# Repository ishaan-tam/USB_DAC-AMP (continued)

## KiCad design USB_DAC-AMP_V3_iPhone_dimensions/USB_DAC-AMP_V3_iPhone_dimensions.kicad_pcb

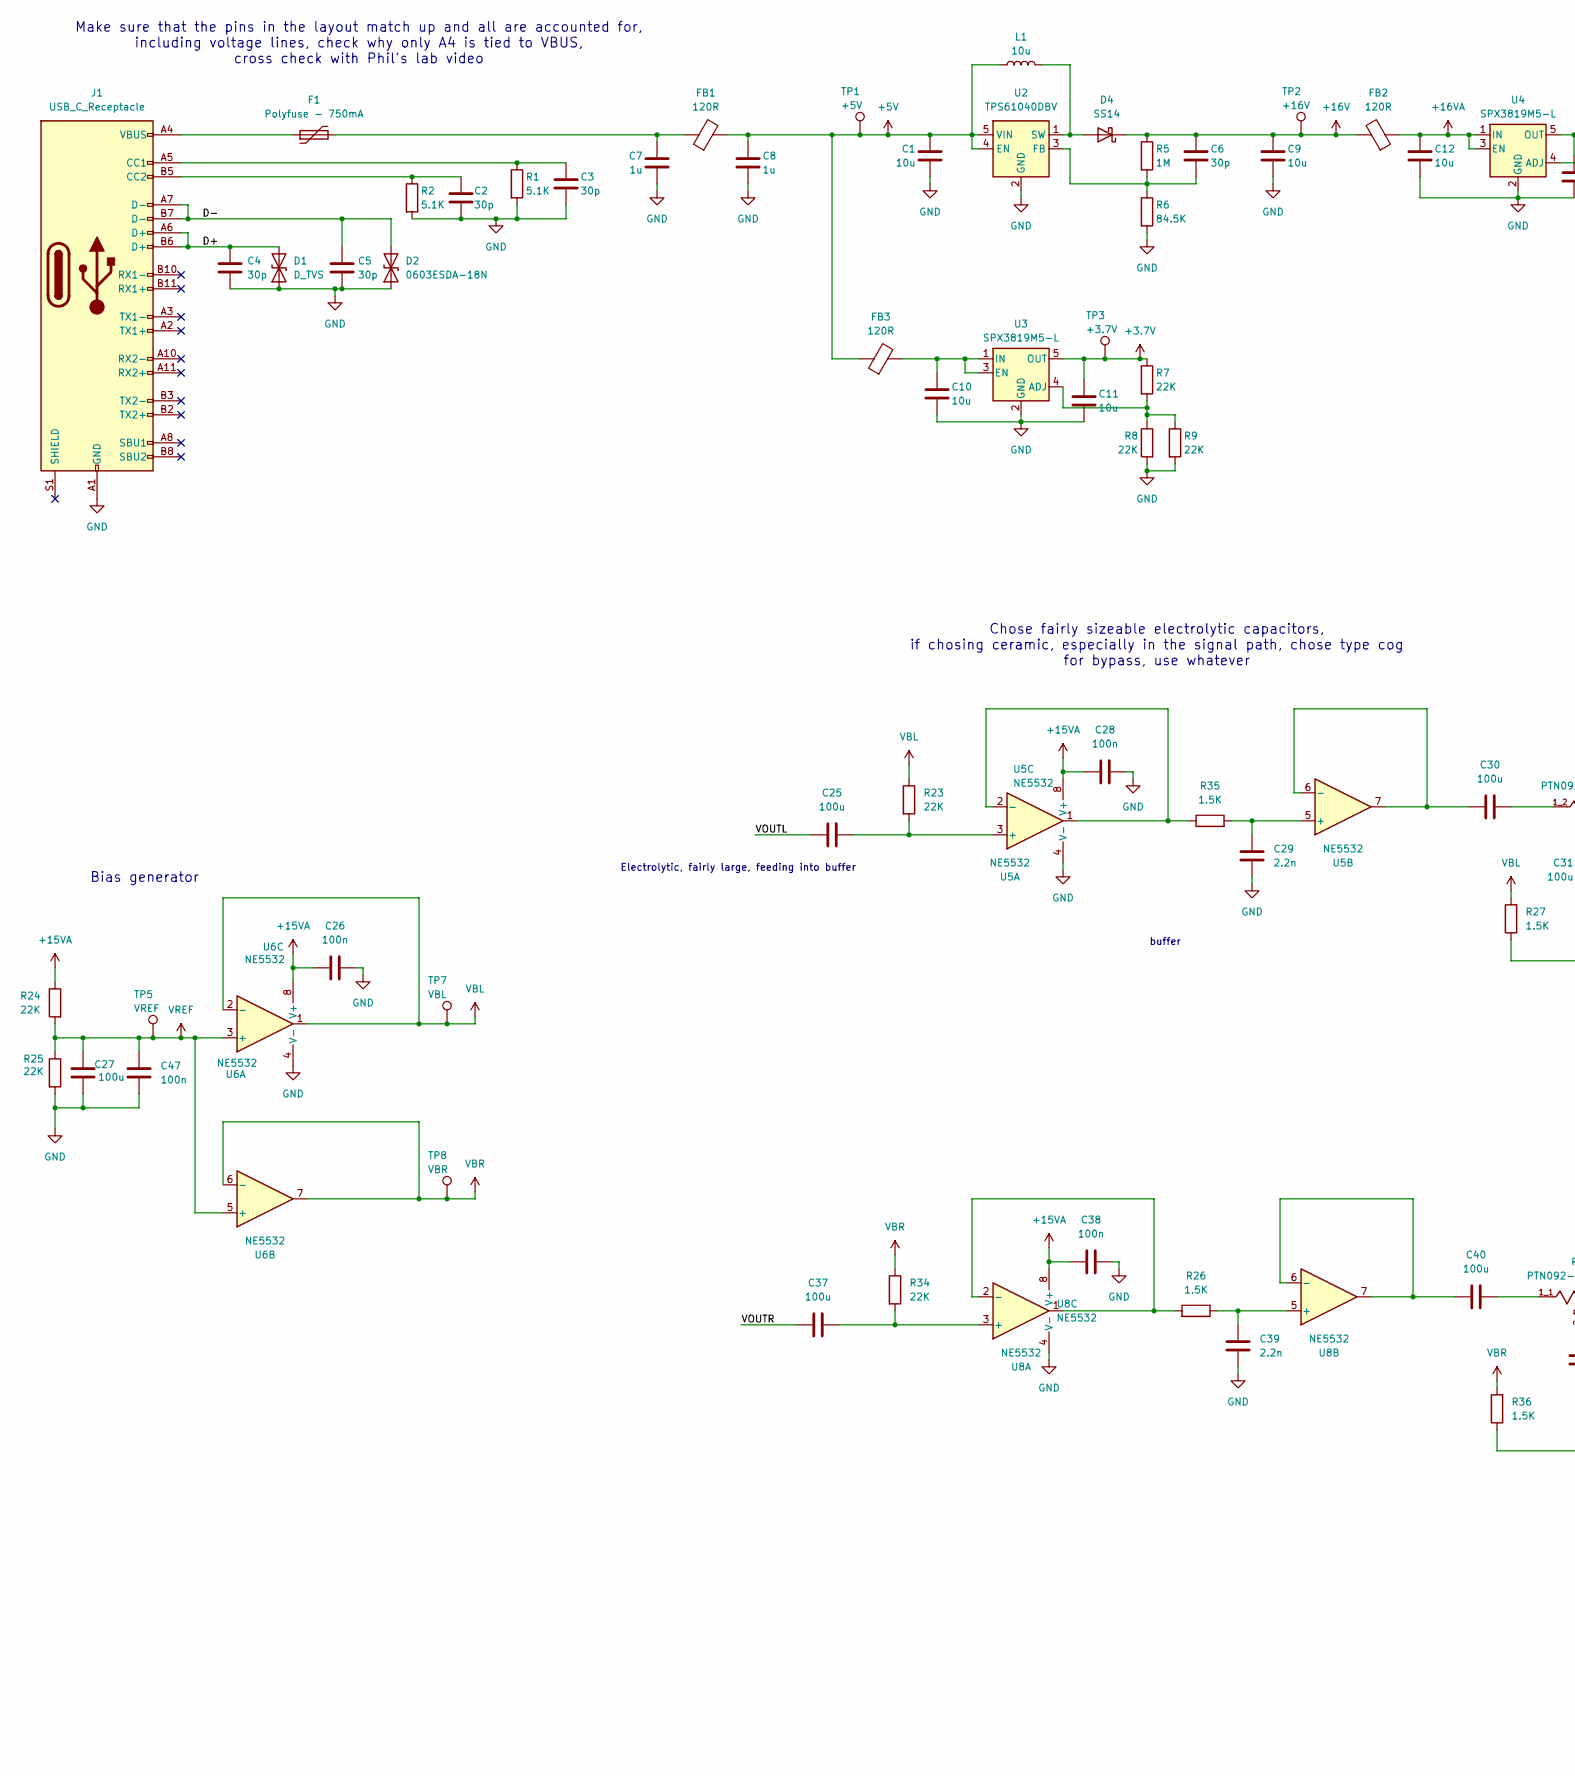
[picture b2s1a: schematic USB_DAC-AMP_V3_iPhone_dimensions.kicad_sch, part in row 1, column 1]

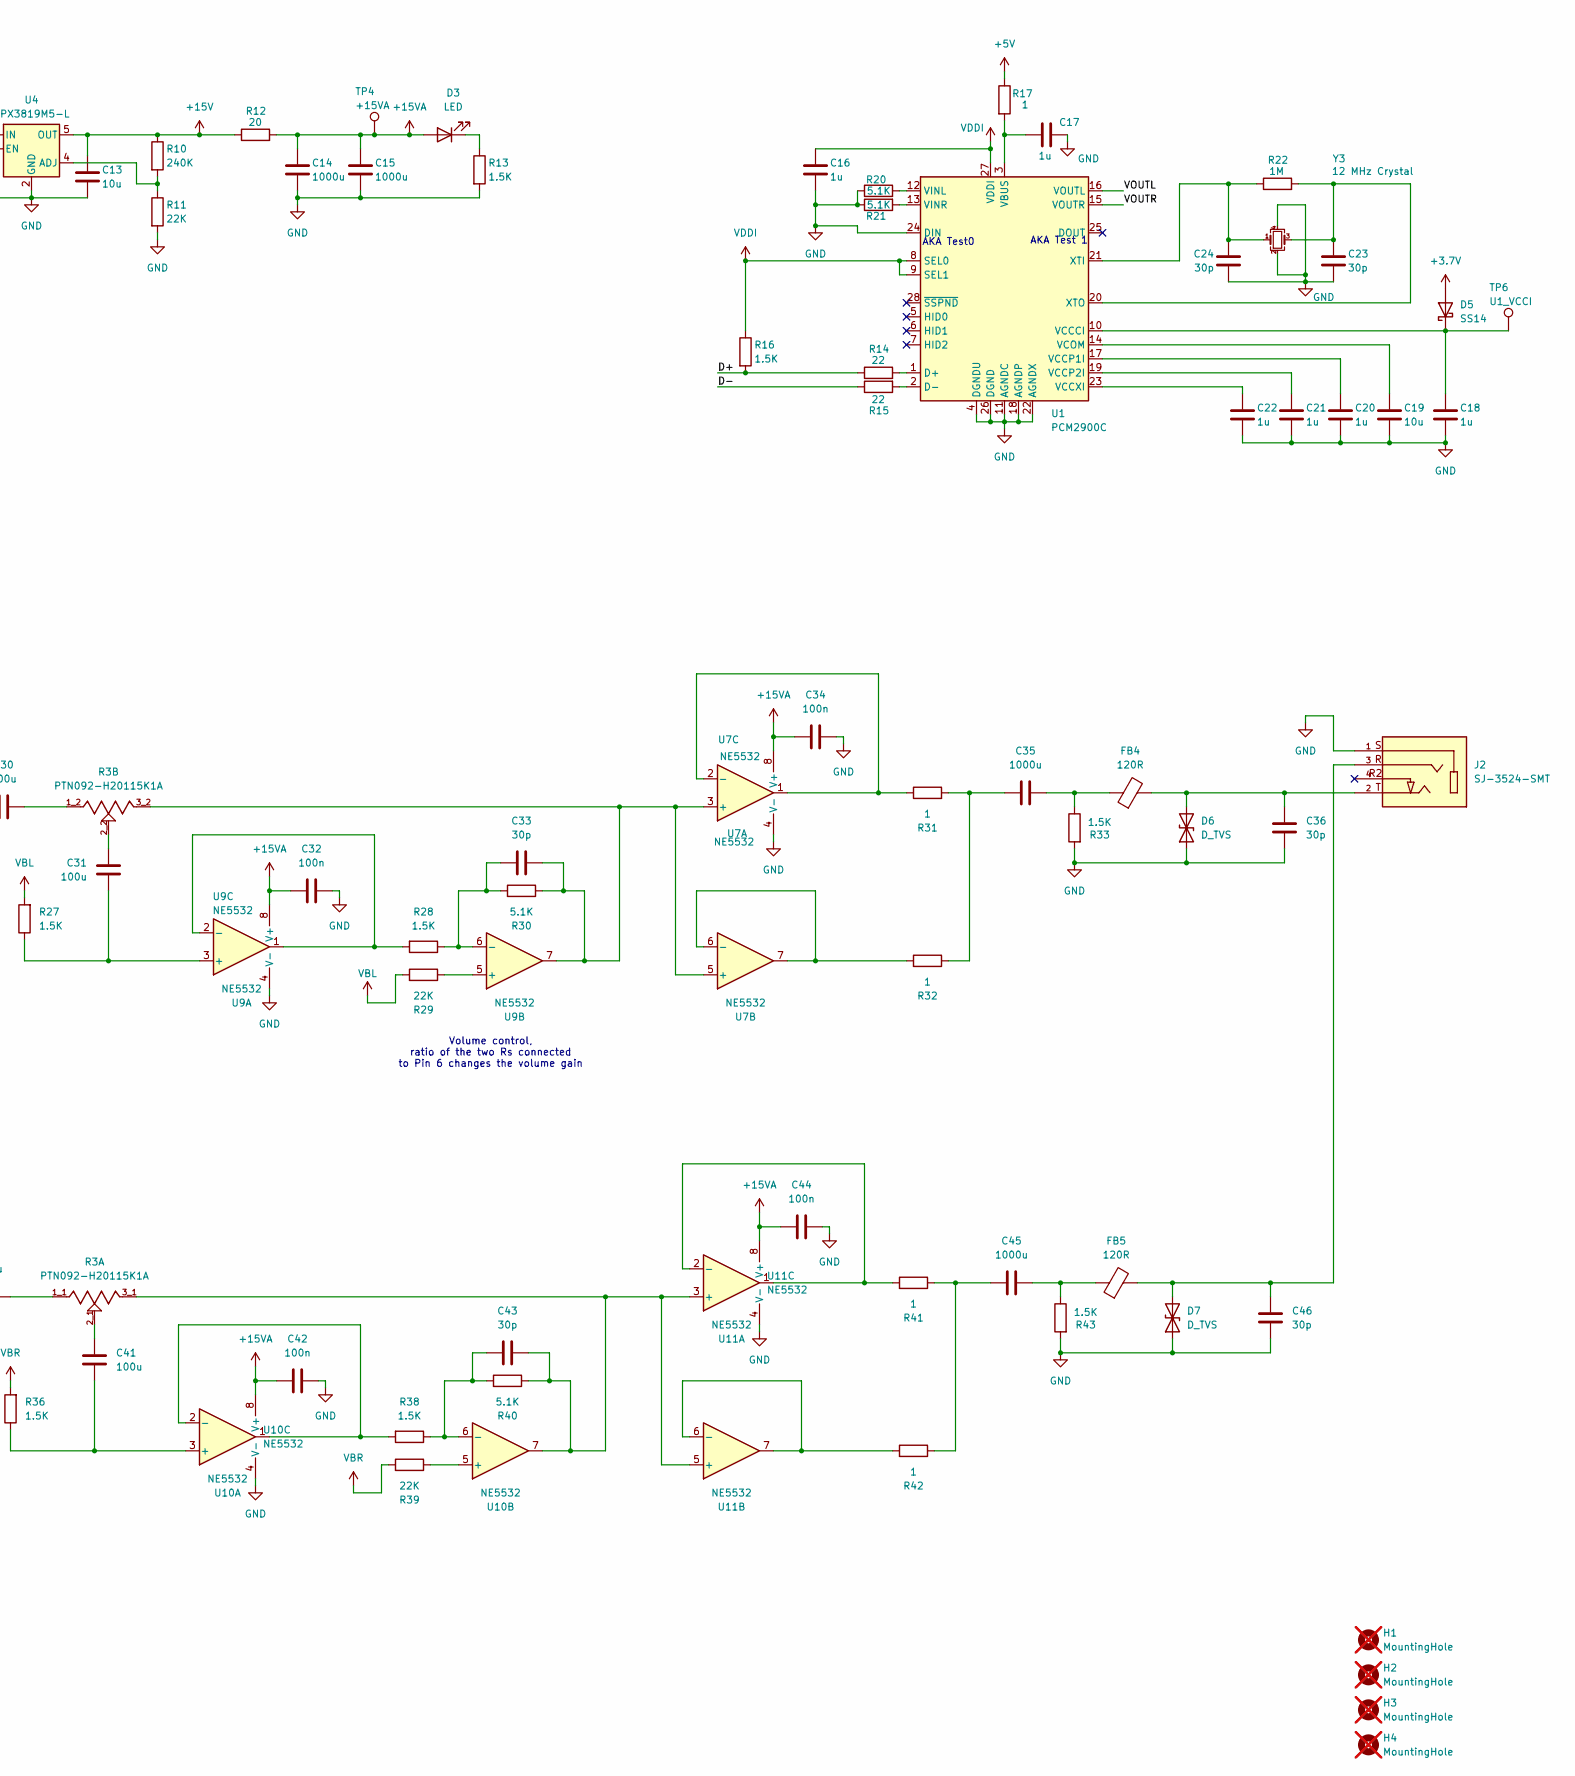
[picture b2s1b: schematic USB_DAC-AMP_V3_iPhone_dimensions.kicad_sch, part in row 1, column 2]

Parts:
C1, C9, C10, C11, C12, C13, C19: 10u; C_0603_1608Metric_Pad1.08x0.95mm_HandSolder; LCSC C1035
C2, C3, C4, C5, C6, C23, C24, C33, C36, C43, C46: 30p; C_0603_1608Metric_Pad1.08x0.95mm_HandSolder; LCSC C1658
C7, C8, C16, C17, C18, C20, C21, C22: 1u; C_0603_1608Metric_Pad1.08x0.95mm_HandSolder; LCSC C1592
C14, C15, C35, C45: 1000u; CP_EIA-7343-43_Kemet-X_HandSolder; LCSC C696799
C25, C27, C30, C31, C40, C41: 100u; CP_EIA-7343-43_Kemet-X_HandSolder; LCSC C132558
C26, C28, C32, C34, C38, C42, C44, C47: 100n; C_0603_1608Metric_Pad1.08x0.95mm_HandSolder; LCSC C1590
C29, C39: 2.2n; C_0603_1608Metric_Pad1.08x0.95mm_HandSolder; LCSC C1028
C37: 100u; CP_EIA-7343-15_Kemet-W; LCSC C1002
D1, D6, D7: D_TVS; D_0603_1608Metric_Pad1.05x0.95mm_HandSolder
D2: 0603ESDA-18N; D_0603_1608Metric_Pad1.05x0.95mm_HandSolder
D3: LED; LED_0603_1608Metric_Pad1.05x0.95mm_HandSolder
D4, D5: SS14; D_SMA
F1: Polyfuse - 750mA; Fuse_0603_1608Metric_Pad1.05x0.95mm_HandSolder
FB1, FB2, FB3, FB4, FB5: 120R; R_0603_1608Metric_Pad0.98x0.95mm_HandSolder
H1, H2, H3, H4: MountingHole; MountingHole_3.5mm; not fitted
J1: USB_C_Receptacle; USB_C_Receptacle_GCT_USB4105-xx-A_16P_TopMnt_Horizontal
J2: SJ-3524-SMT; PARTREV 1.03; DigiKey_Part_Number CP-3524SJCT-ND
L1: 10u; L_0805_2012Metric_Pad1.05x1.20mm_HandSolder
R1, R2, R20, R21, R30, R40: 5.1K; R_0603_1608Metric_Pad0.98x0.95mm_HandSolder
R3: PTN092-H20115K1A; TRIM_PTN092-H20115K1A; PARTREV 1.01; DigiKey_Part_Number 2223-PTN092-H20115K1A-ND
R5, R22: 1M; R_0603_1608Metric_Pad0.98x0.95mm_HandSolder
R6: 84.5K; R_0603_1608Metric_Pad0.98x0.95mm_HandSolder
R7, R8, R9, R11, R23, R24, R25, R29, R34, R39: 22K; R_0603_1608Metric_Pad0.98x0.95mm_HandSolder
R10: 240K; R_0603_1608Metric_Pad0.98x0.95mm_HandSolder
R12: 20; R_0603_1608Metric_Pad0.98x0.95mm_HandSolder
R13, R16, R26, R27, R28, R33, R35, R36, R38, R43: 1.5K; R_0603_1608Metric_Pad0.98x0.95mm_HandSolder
R14, R15: 22; R_0603_1608Metric_Pad0.98x0.95mm_HandSolder
R17, R31, R32, R41, R42: 1; R_0603_1608Metric_Pad0.98x0.95mm_HandSolder
TP1: +5V; TestPoint_Pad_1.0x1.0mm
TP2: +16V; TestPoint_Pad_1.0x1.0mm
TP3: +3.7V; TestPoint_Pad_1.0x1.0mm
TP4: +15VA; TestPoint_Pad_1.0x1.0mm
TP5: VREF; TestPoint_Pad_1.0x1.0mm
TP6: U1_VCCI; TestPoint_Pad_1.0x1.0mm
TP7: VBL; TestPoint_Pad_1.0x1.0mm
TP8: VBR; TestPoint_Pad_1.0x1.0mm
U1: PCM2900C; SSOP-28_5.3x10.2mm_P0.65mm
U2: TPS61040DBV; SOT-23-5
U3, U4: SPX3819M5-L; SOT-23-5
U5, U6, U7, U8, U9, U10, U11: NE5532; SOIC-8_5.3x5.3mm_P1.27mm
Y3: 12 MHz Crystal; Crystal_SMD_3225-4Pin_3.2x2.5mm

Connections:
+3.7V: C11.1, D5.2 (A), R7.1, TP3.1, U3.5 (OUT)
+5V: C1.1, C8.1, FB1.2, FB3.1, L1.1, R17.1, TP1.1, U2.4 (EN), U2.5 (VIN)
+15V: C13.1, R10.1, R12.1, U4.5 (OUT)
+15VA: C14.1, C15.1, C26.1, C28.1, C32.1, C34.1, C38.1, C42.1, C44.1, D3.2 (A), R12.2, R24.1, TP4.1, U5.8 (V+), U6.8 (V+), U7.8 (V+), U8.8 (V+), U9.8 (V+), U10.8 (V+), U11.8 (V+)
+16V: C6.1, C9.1, D4.1 (K), FB2.2, R5.1, TP2.1
+16VA: C12.1, FB2.1, U4.1 (IN), U4.3 (EN)
/D+: C4.1, D1.2 (A2), J1.A6 (D+), J1.B6 (D+), R14.1, R16.2; also elsewhere on the board
/D-: C5.1, D2.2 (A2), J1.A7 (D-), J1.B7 (D-), R15.1; also elsewhere on the board
/VOUTL: C25.1, U1.16 (VOUTL)
/VOUTR: C37.1, U1.15 (VOUTR)
GND: C1.2, C2.2, C3.2, C4.2, C5.2, C7.2, C8.2, C9.2, C10.2, C11.2, C12.2, C13.2, C14.2, C15.2, C16.2, C17.2, C18.2, C19.2, C20.2, C21.2, C22.2, C23.2, C24.2, C26.2, C27.1, C28.2, C29.1, C32.2, C34.2, C36.1, C38.2, C39.1, C42.2, C44.2, C46.1, C47.1, D1.1 (A1), D2.1 (A1), D6.1 (A1), D7.1 (A1), J1.A1 (GND), J1.A12 (GND), J1.B1 (GND), J1.B12 (GND), J2.1, R1.2, R2.2, R6.2, R8.2, R9.2, R11.2, R13.2, R20.1, R21.1, R25.2, R33.2, R43.2, U1.4 (DGNDU), U1.11 (AGNDC), U1.18 (AGNDP), U1.22 (AGNDX), U1.24 (DIN), U1.26 (DGND), U2.2 (GND), U3.2 (GND), U4.2 (GND), U5.4 (V-), U6.4 (V-), U7.4 (V-), U8.4 (V-), U9.4 (V-), U10.4 (V-), U11.4 (V-), Y3.2, Y3.4; also elsewhere on the board
unnamed: C7.1, F1.2, FB1.1
unnamed: C30.2, R3.1_2
unnamed: C31.2, R3.2_2
unnamed: C35.1, R31.2, R32.1
unnamed: C35.2, FB4.1, R33.1
unnamed: C40.2, R3.1_1
unnamed: C41.2, R3.2_1, R21.1_1
unnamed: C45.1, R41.1, R42.1
unnamed: C45.2, FB5.1, R43.1
unnamed: D3.1 (K), R13.1
unnamed: D4.2 (A), L1.2, U2.1 (SW)
unnamed: C18.1, D5.1 (K), TP6.1, U1.10 (VCCCI)
unnamed 26: C36.2, D6.2 (A2), FB4.2, J2.2; also elsewhere on the board
unnamed 27: C46.2, D7.2 (A2), FB5.2, J2.3; also elsewhere on the board
unnamed 28: F1.1, J1.A4 (VBUS), J1.A9 (VBUS), J1.B4 (VBUS), J1.B9 (VBUS); also elsewhere on the board
unnamed 29: C3.1, J1.A5 (CC1), R1.1; also elsewhere on the board
unnamed 30: C2.1, J1.B5 (CC2), R2.1; also elsewhere on the board
unnamed: R14.2, U1.1 (D+)
unnamed: R15.2, U1.2 (D-)
unnamed: C17.1, R17.2, U1.3 (VBUS)
unnamed: C20.1, U1.17 (VCCP1I)
unnamed: C21.1, U1.19 (VCCP2I)
unnamed: C22.1, U1.23 (VCCXI)
unnamed: C19.1, U1.14 (VCOM)
unnamed: R20.2, U1.12 (VINL)
unnamed 39: R21.2, U1.13 (VINR); also elsewhere on the board
unnamed: C24.1, R22.1, U1.21 (XTI), Y3.1
unnamed: C23.1, R22.2, U1.20 (XTO), Y3.3
unnamed: C6.2, R5.2, R6.1, U2.3 (FB)
unnamed: R7.2, R8.1, R9.1, U3.4 (ADJ)
unnamed: C10.1, FB3.2, U3.1 (IN), U3.3 (EN)
unnamed: R10.2, R11.1, U4.4 (ADJ)
unnamed: C25.2, R21.3_2, R23.2, U5.3 (+)
unnamed: R35.1, U5.1, U5.2 (-)
unnamed: C29.2, R35.2, U5.5 (+)
unnamed: C30.1, U5.6 (-), U5.7
unnamed: C33.2, R3.3_2, R30.1, U7.3 (+), U7.5 (+), U9.7
unnamed: R31.1, U7.1, U7.2 (-)
unnamed: R32.2, U7.6 (-), U7.7
unnamed: C37.2, R34.2, U8.3 (+)
unnamed: R26.2, U8.1, U8.2 (-)
unnamed: C39.2, R26.1, U8.5 (+)
unnamed: C40.1, U8.6 (-), U8.7
unnamed: C31.1, R21.3_1, R27.1, U9.3 (+)
unnamed: R28.2, U9.1, U9.2 (-)
unnamed: R29.1, U9.5 (+)
unnamed: C33.1, R28.1, R30.2, U9.6 (-)
unnamed: C41.1, R36.1, U10.3 (+)
unnamed: R38.2, U10.1, U10.2 (-)
unnamed: R39.1, U10.5 (+)
unnamed: C43.1, R38.1, R40.2, U10.6 (-)
unnamed: C43.2, R3.3_1, R40.1, U10.7, U11.3 (+), U11.5 (+)
unnamed: R41.2, U11.1, U11.2 (-)
unnamed: R42.2, U11.6 (-), U11.7
VBL: R23.1, R27.2, R29.2, TP7.1, U6.1, U6.2 (-)
VBR: R34.1, R36.2, R39.2, TP8.1, U6.6 (-), U6.7
VDDI: C16.1, R16.1, U1.8 (SEL0), U1.9 (SEL1), U1.27 (VDDI)
VREF: C27.2, C47.2, R24.2, R25.1, TP5.1, U6.3 (+), U6.5 (+)

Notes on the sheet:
Chose fairly sizeable electrolytic capacitors, if chosing ceramic, especially in the signal path, chose type cog for bypass, use whatever
AKA Test 1
buffer
Bias generator
Electrolytic, fairly large, feeding into buffer
Make sure that the pins in the layout match up and all are accounted for, including voltage lines, check why only A4 is tied to VBUS, cross check with Phil's lab video
AKA Test0
Volume control, ratio of the two Rs connected to Pin 6 changes the volume gain

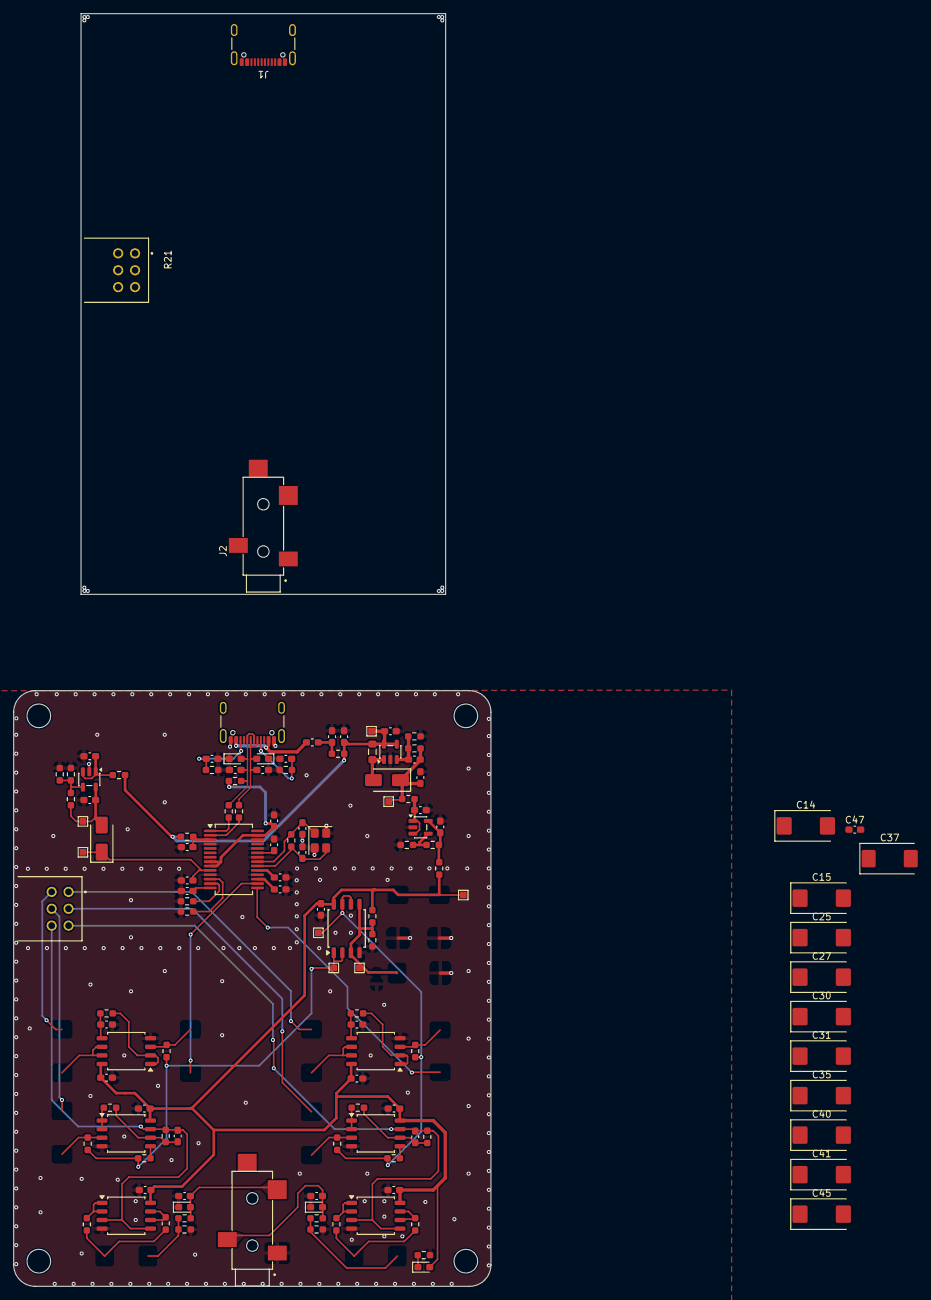
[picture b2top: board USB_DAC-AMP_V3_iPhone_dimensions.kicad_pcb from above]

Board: 4 copper layers, 70.7 x 88.2 mm, 129 parts (0 on the bottom side), 69 nets.

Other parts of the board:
J1#2: USB_C_Receptacle; USB_C_Receptacle_GCT_USB4105-xx-A_16P_TopMnt_Horizontal
J2#2: SJ-3524-SMT
R21#2: 1.5k; R_0603_1608Metric_Pad0.98x0.95mm_HandSolder

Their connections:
/D+: J1#2.A6 (D+), J1#2.B6 (D+); also elsewhere on the board
/D-: J1#2.A7 (D-), J1#2.B7 (D-); also elsewhere on the board
GND: J1#2.A1 (GND), J1#2.A12 (GND), J1#2.B1 (GND), J1#2.B12 (GND), J2#2.1, R21#2.1; also elsewhere on the board
unnamed 26: J2#2.2; also elsewhere on the board
unnamed 27: J2#2.3; also elsewhere on the board
unnamed 28: J1#2.A4 (VBUS), J1#2.A9 (VBUS), J1#2.B4 (VBUS), J1#2.B9 (VBUS); also elsewhere on the board
unnamed 29: J1#2.A5 (CC1); also elsewhere on the board
unnamed 30: J1#2.B5 (CC2); also elsewhere on the board
unnamed 39: R21#2.2; also elsewhere on the board

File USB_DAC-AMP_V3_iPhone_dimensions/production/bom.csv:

Designator,Footprint,Quantity,Value,LCSC Part #
"C1, C10, C11, C12, C13, C19, C9",0603,7,10u,
"C14, C15, C35, C45",CP_EIA-7343-43_Kemet-X_HandSolder,4,1000u,
"C16, C17, C18, C20, C21, C22, C7, C8",0603,8,1u,
"C2, C23, C24, C3, C33, C36, C4, C43, C46, C5, C6",0603,11,30p,
"C25, C27, C30, C31, C40, C41",CP_EIA-7343-43_Kemet-X_HandSolder,6,100u,
"C26, C28, C32, C34, C38, C42, C44, C47",0603,8,100n,
"C29, C39",0603,2,2.2n,
C37,CP_EIA-7343-15_Kemet-W,1,100u,
"D1, D6, D7",0603,3,D_TVS,
D2,0603,1,0603ESDA-18N,
D3,0603,1,LED,
"D4, D5",D_SMA,2,SS14,
F1,0603,1,Polyfuse - 750mA,
"FB1, FB2, FB3, FB4, FB5",0603,5,120R,
J1,USB_C_Receptacle_GCT_USB4105-xx-A_16P_TopMnt_Horizontal,1,USB_C_Receptacle,
J2,SJ-3524-SMT,1,SJ-3524-SMT,
L1,0805,1,10u,
"R1, R2, R30, R40",0603,4,5.1K,
R10,0603,1,240K,
"R11, R23, R24, R25, R29, R34, R39, R7, R8, R9",0603,10,22K,
R12,0603,1,20,
"R13, R16, R20, R21, R26, R27, R28, R33, R35, R36, R38, R43",0603,12,1.5K,
"R14, R15",0603,2,22,
"R17, R31, R32, R41, R42",0603,5,1,
"R22, R5",0603,2,1M,
R3,TRIM_PTN092-H20115K1A,1,PTN092-H20115K1A,
R6,0603,1,84.5K,
TP1,TestPoint_Pad_1.0x1.0mm,1,+5V,
TP2,TestPoint_Pad_1.0x1.0mm,1,+16V,
TP3,TestPoint_Pad_1.0x1.0mm,1,+3.7V,
TP4,TestPoint_Pad_1.0x1.0mm,1,+15VA,
TP5,TestPoint_Pad_1.0x1.0mm,1,VREF,
TP6,TestPoint_Pad_1.0x1.0mm,1,U1_VCCI,
TP7,TestPoint_Pad_1.0x1.0mm,1,VBL,
TP8,TestPoint_Pad_1.0x1.0mm,1,VBR,
U1,SSOP-28_5.3x10.2mm_P0.65mm,1,PCM2900C,
"U10, U11, U5, U6, U7, U8, U9",SOIC-8_5.3x5.3mm_P1.27mm,7,NE5532,
U2,SOT-23-5,1,TPS61040DBV,
"U3, U4",SOT-23-5,2,SPX3819M5-L,
Y3,Crystal_SMD_3225-4Pin_3.2x2.5mm,1,12 MHz Crystal,

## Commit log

2025-12-20 Revise README with detailed project overview
    Updated project description, status, architecture, design decisions, and development philosophy.
2025-12-21 Add build plan and checklist for USB DAC project
    Added a detailed build plan and checklist for the USB DAC headphone amp project, outlining phases from architecture locking to testing and refinement.
2025-12-24 Schematic USB and IC design mostly complete
2025-12-27 finished USB_DAC-AMP schematic
2025-12-27 finished V1 footprint assignments
2025-12-30 created V4 to change board dimensions, update schematic
    changed out caps to be electrolytic
    board dimensions are now whole numbers
2025-12-31 updated V4
2026-01-02 Finished V4 layout
2026-01-04 Submitted V1 to Kicad
2026-01-12 misc files upload
